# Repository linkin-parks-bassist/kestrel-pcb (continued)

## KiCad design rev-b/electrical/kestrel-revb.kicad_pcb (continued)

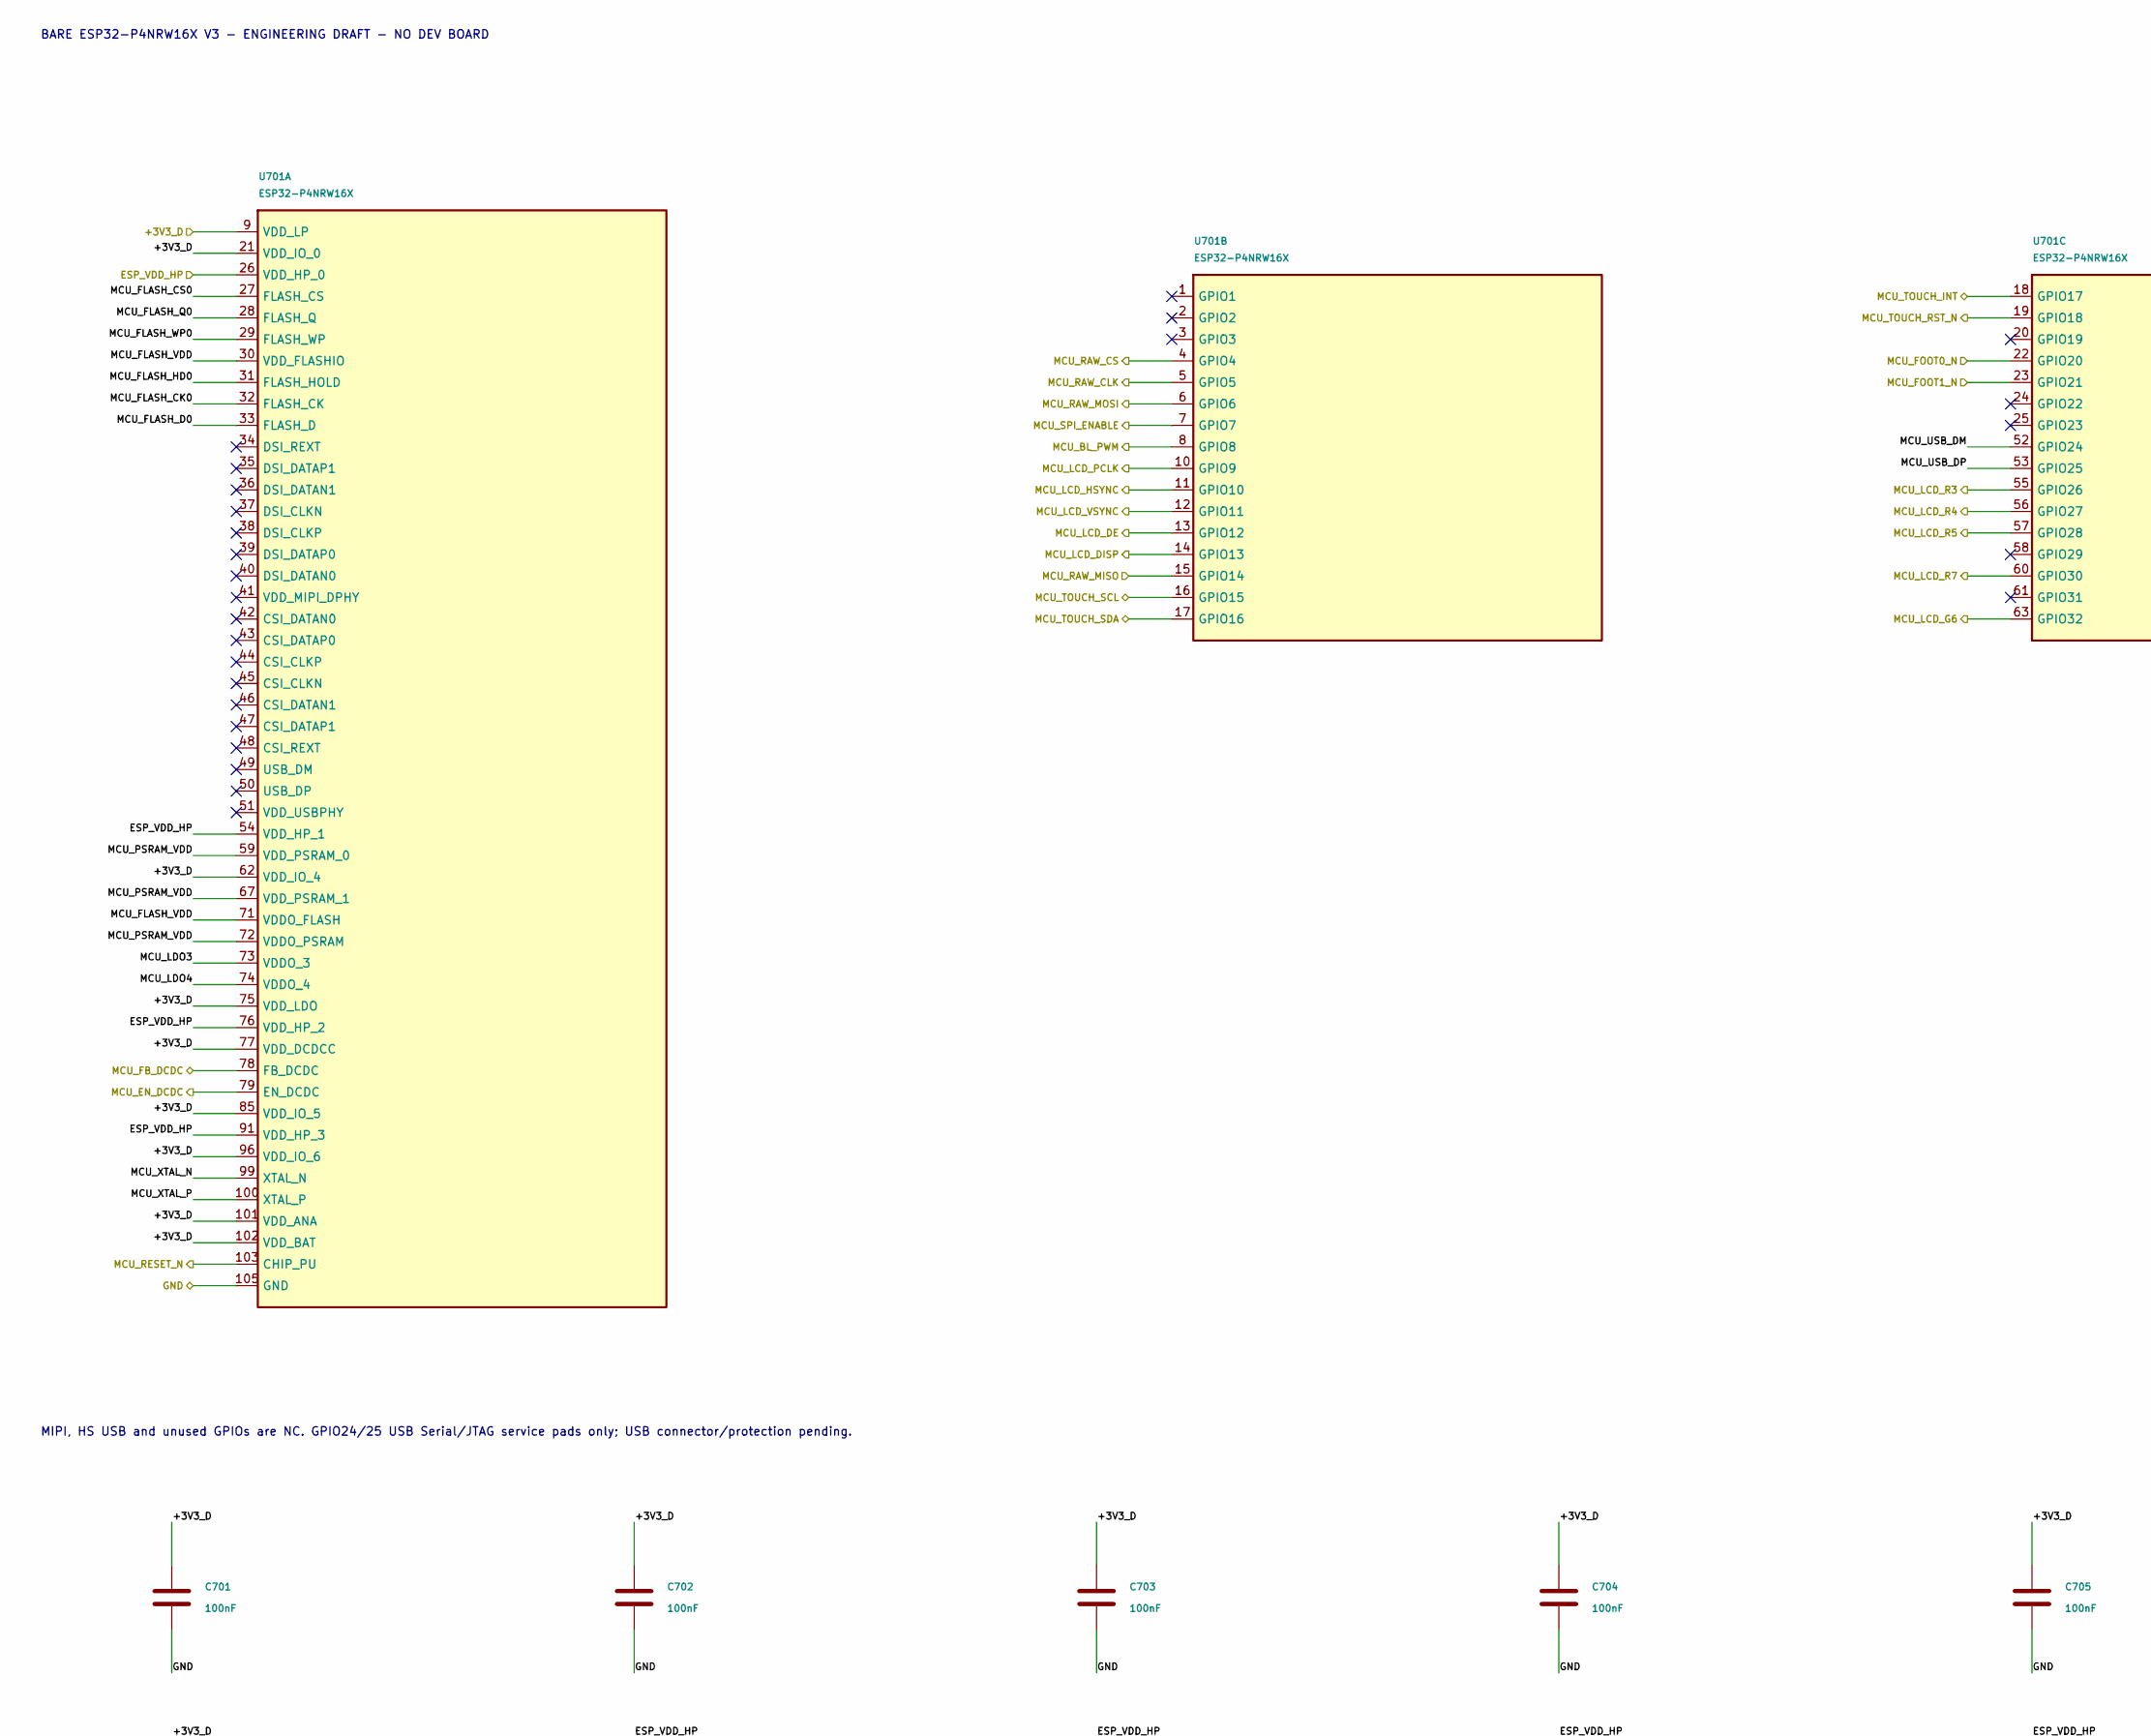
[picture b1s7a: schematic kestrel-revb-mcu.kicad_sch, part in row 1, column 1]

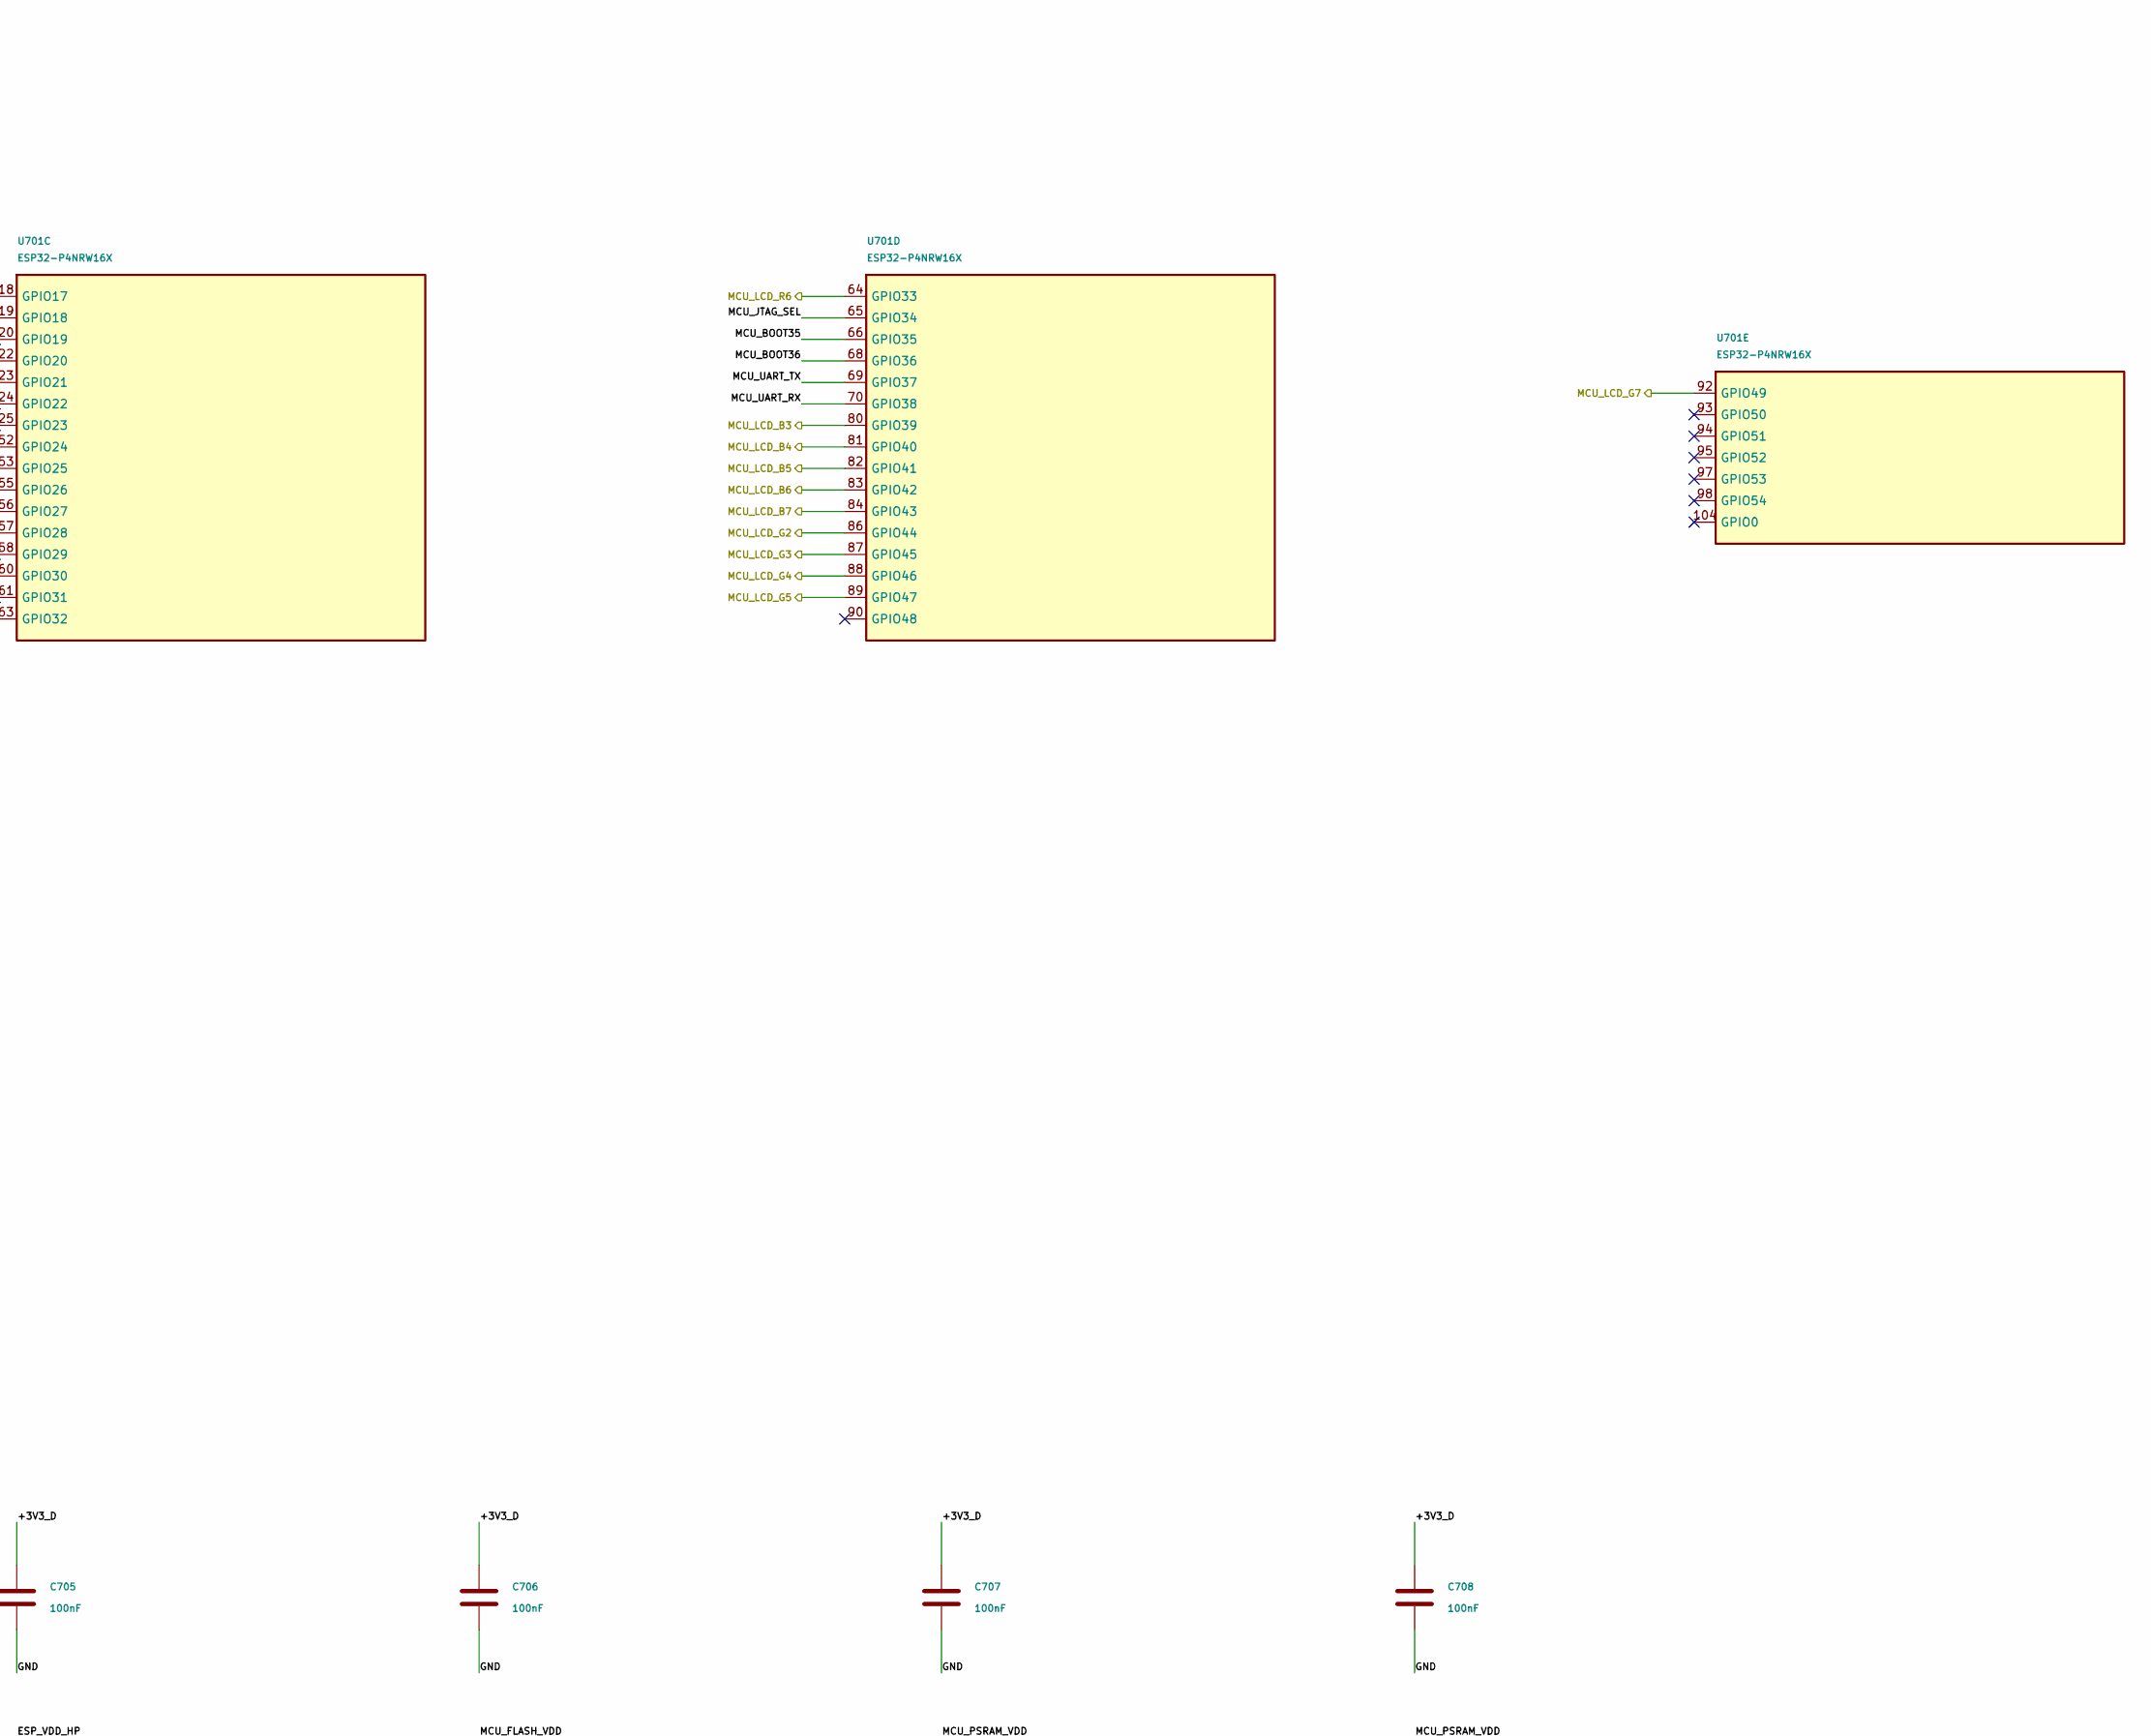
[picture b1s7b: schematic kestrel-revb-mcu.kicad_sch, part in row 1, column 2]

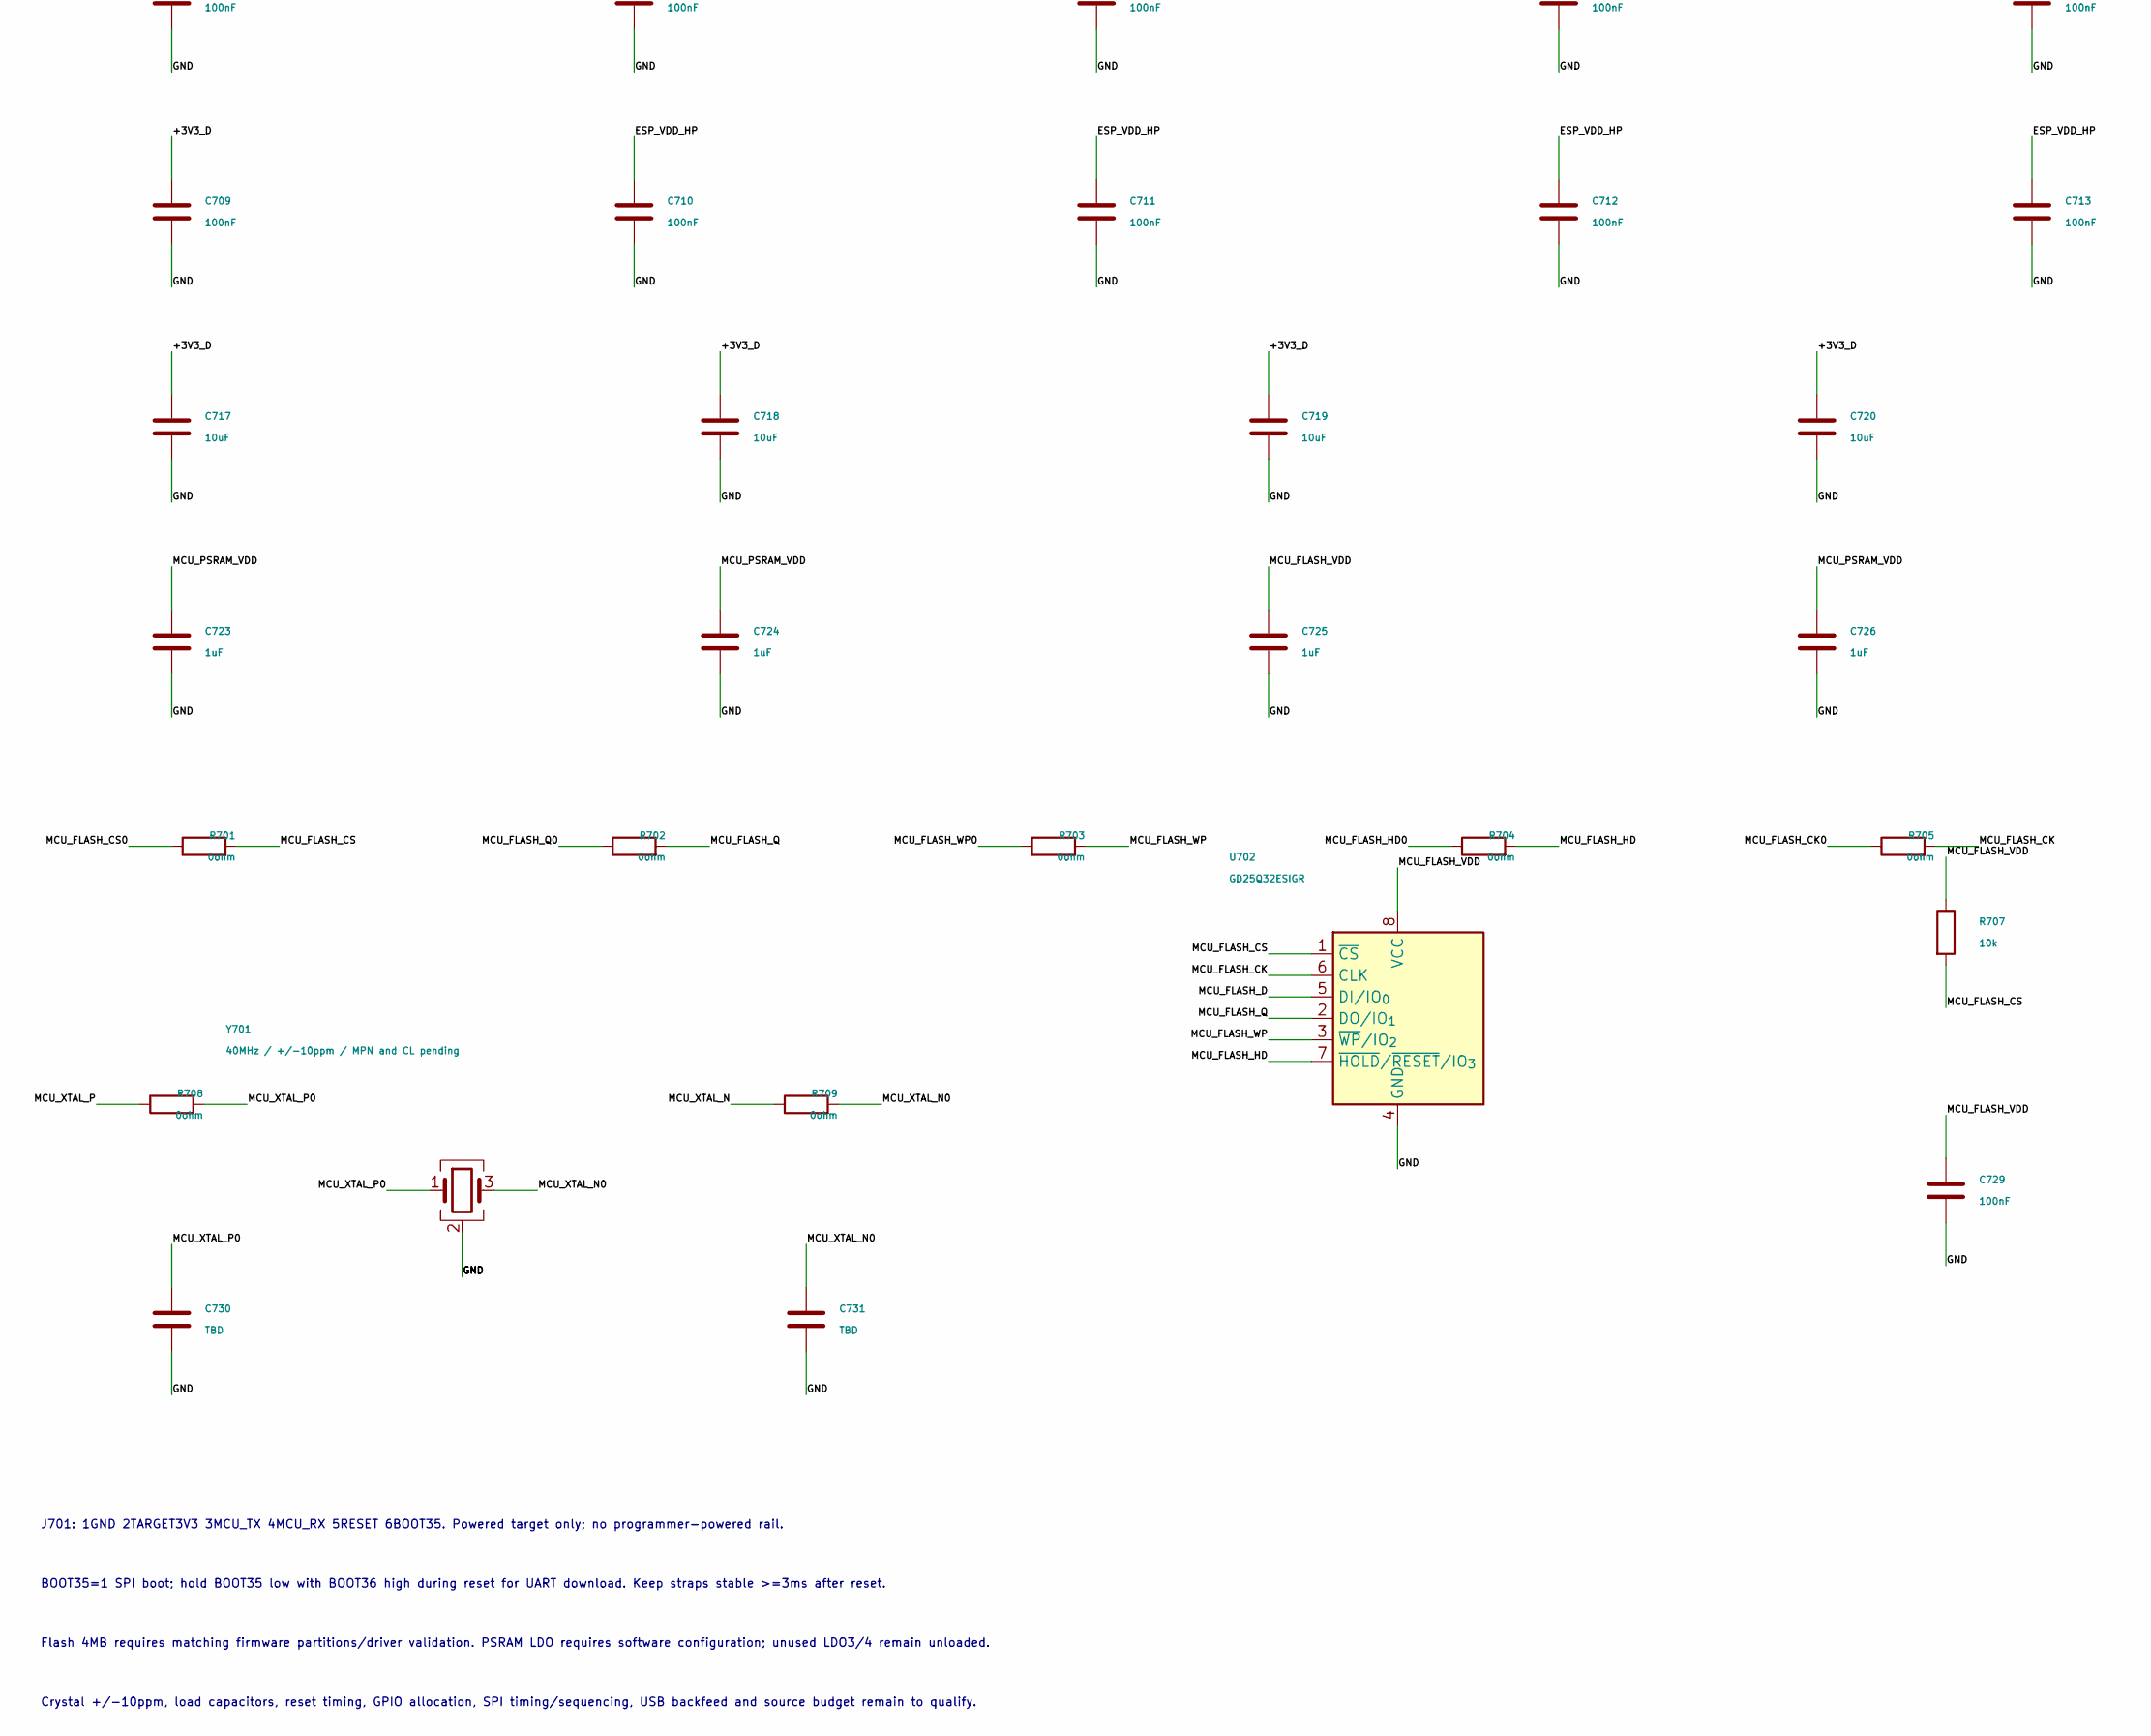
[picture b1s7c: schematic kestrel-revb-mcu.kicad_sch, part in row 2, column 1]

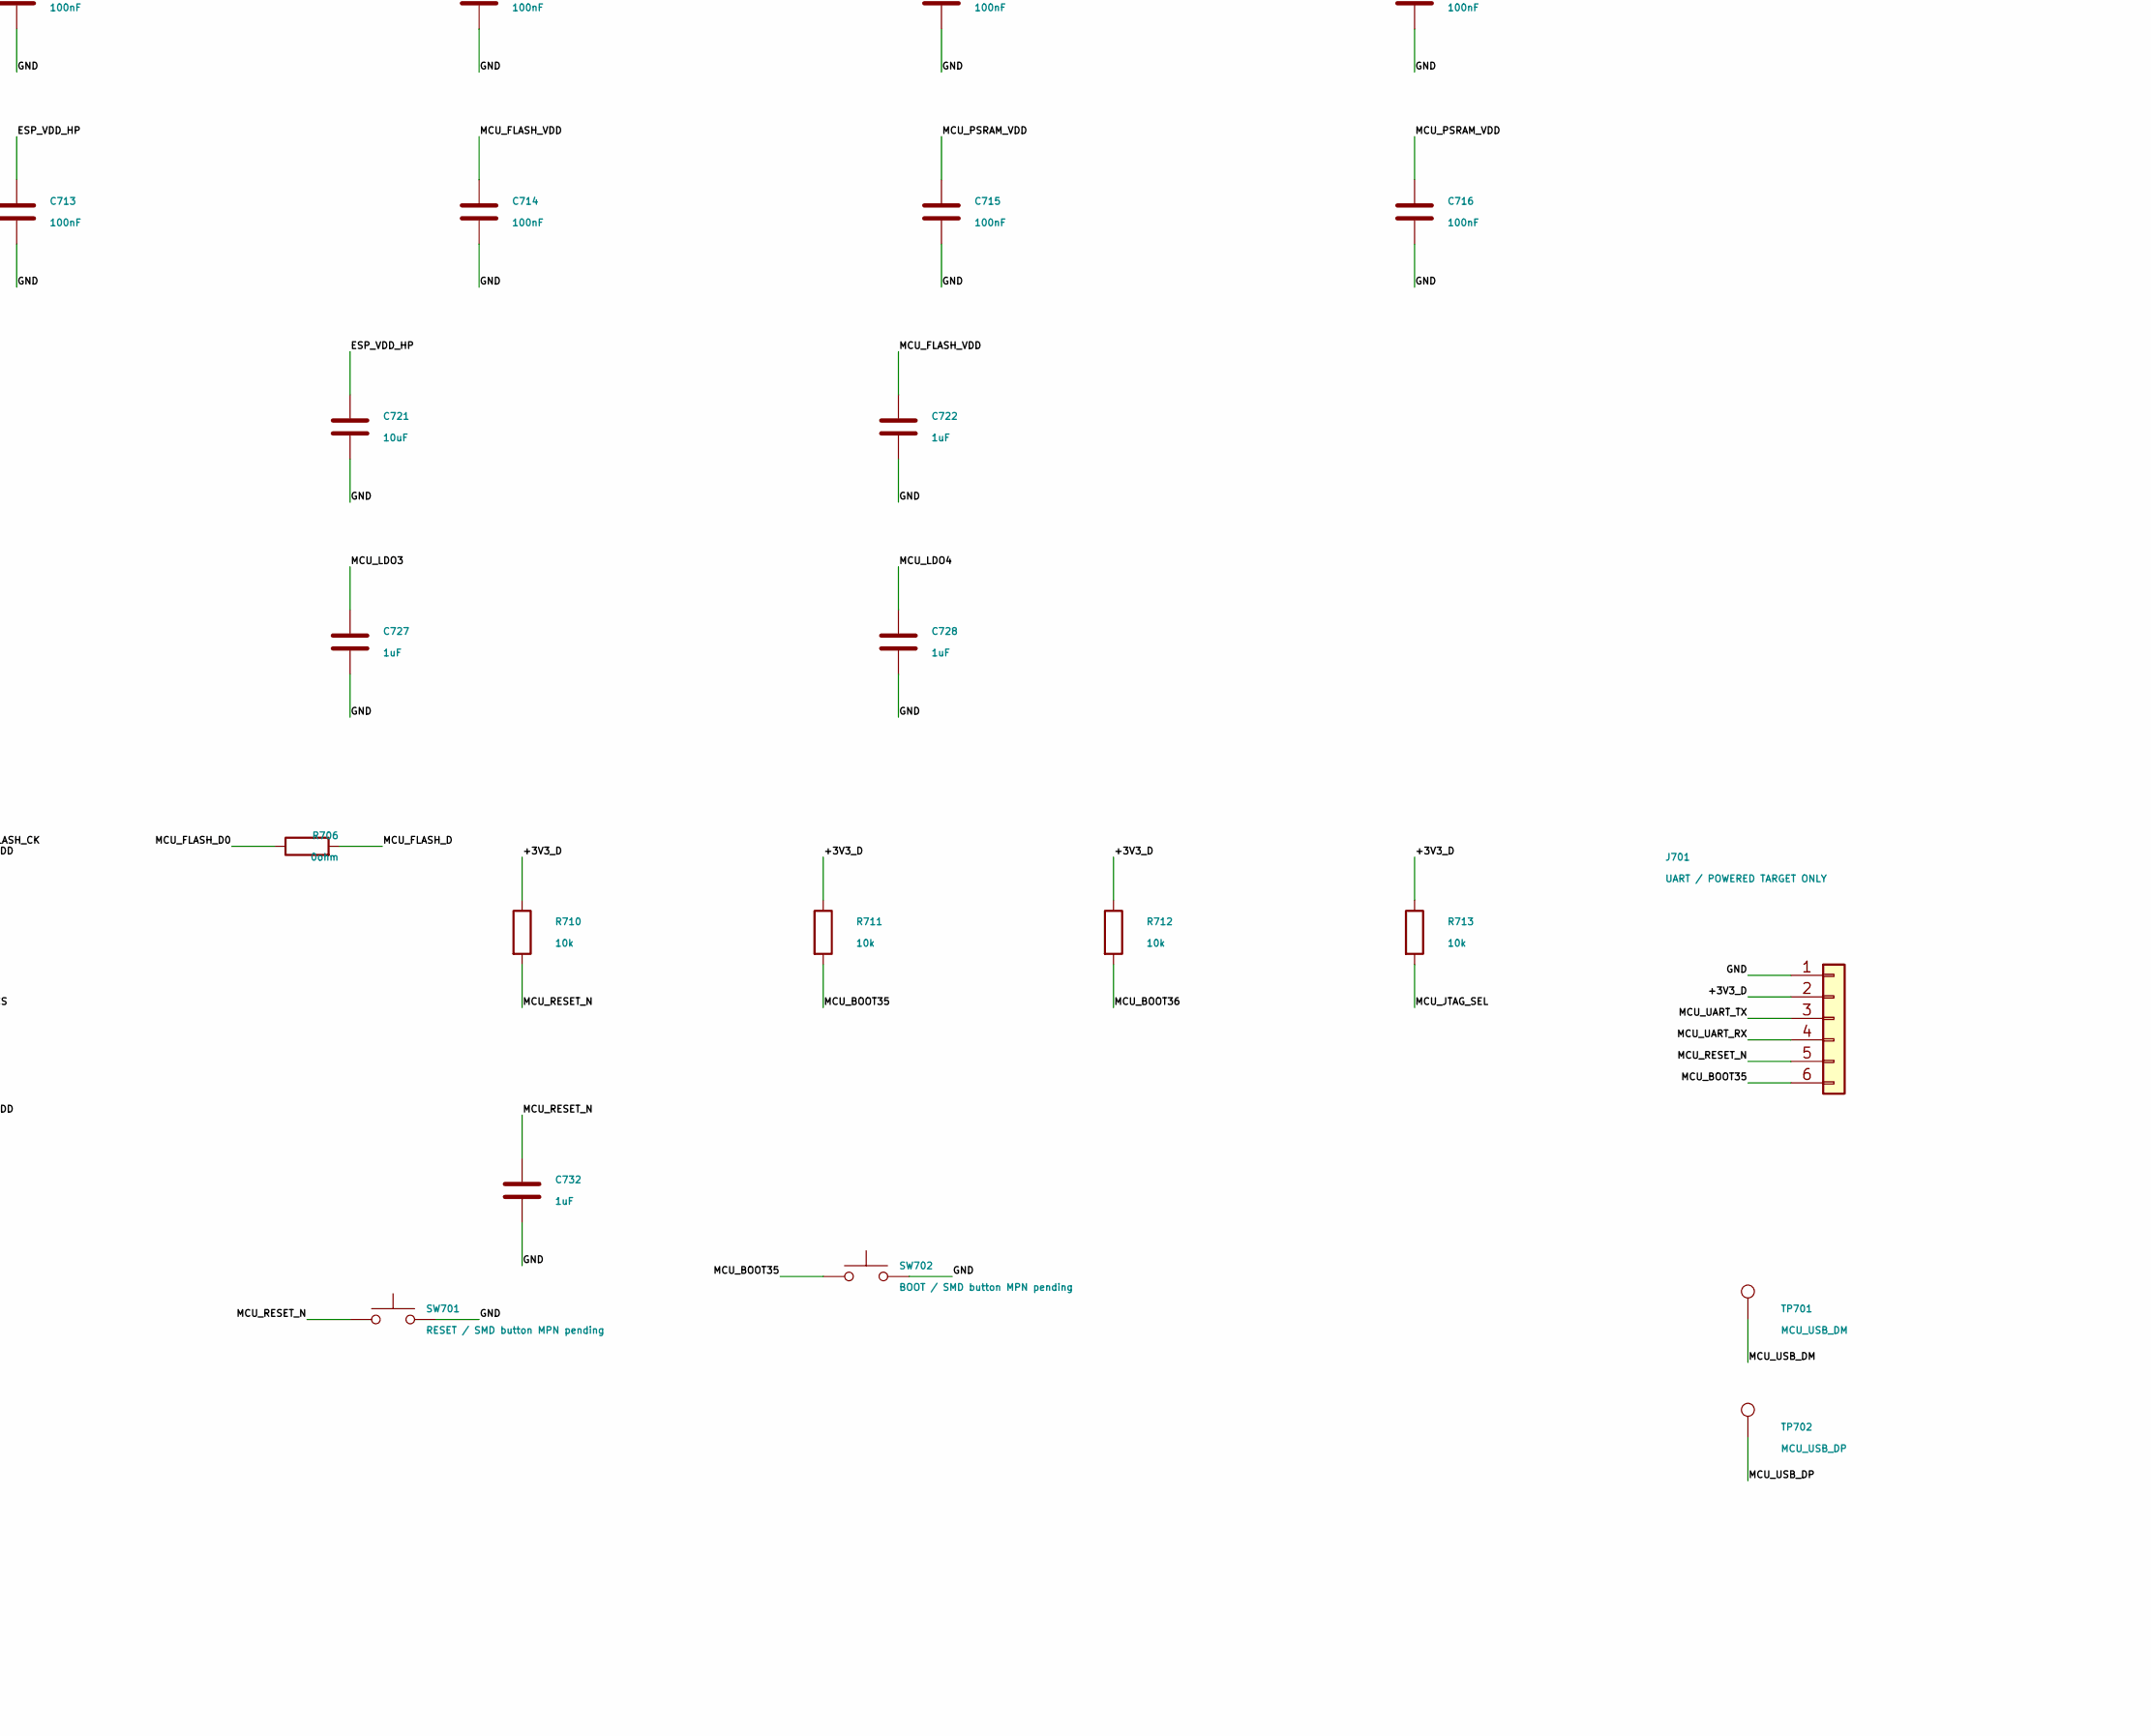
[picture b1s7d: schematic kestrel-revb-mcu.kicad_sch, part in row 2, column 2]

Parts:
C701: 100nF; C_0402_1005Metric; Rating 100nF / 16V X7R +/-10% / at U701 pin 9; MPN CL05B104KO5NNNC; LCSC C1525
C702: 100nF; C_0402_1005Metric; Rating 100nF / 16V X7R +/-10% / at U701 pin 21; MPN CL05B104KO5NNNC; LCSC C1525
C703: 100nF; C_0402_1005Metric; Rating 100nF / 16V X7R +/-10% / at U701 pin 62; MPN CL05B104KO5NNNC; LCSC C1525
C704: 100nF; C_0402_1005Metric; Rating 100nF / 16V X7R +/-10% / at U701 pin 85; MPN CL05B104KO5NNNC; LCSC C1525
C705: 100nF; C_0402_1005Metric; Rating 100nF / 16V X7R +/-10% / at U701 pin 96; MPN CL05B104KO5NNNC; LCSC C1525
C706: 100nF; C_0402_1005Metric; Rating 100nF / 16V X7R +/-10% / at U701 pin 101; MPN CL05B104KO5NNNC; LCSC C1525
C707: 100nF; C_0402_1005Metric; Rating 100nF / 16V X7R +/-10% / at U701 pin 102; MPN CL05B104KO5NNNC; LCSC C1525
C708: 100nF; C_0402_1005Metric; Rating 100nF / 16V X7R +/-10% / at U701 pin 75; MPN CL05B104KO5NNNC; LCSC C1525
C709: 100nF; C_0402_1005Metric; Rating 100nF / 16V X7R +/-10% / at U701 pin 77; MPN CL05B104KO5NNNC; LCSC C1525
C710: 100nF; C_0402_1005Metric; Rating 100nF / 16V X7R +/-10% / at U701 pin 26; MPN CL05B104KO5NNNC; LCSC C1525
C711: 100nF; C_0402_1005Metric; Rating 100nF / 16V X7R +/-10% / at U701 pin 54; MPN CL05B104KO5NNNC; LCSC C1525
C712: 100nF; C_0402_1005Metric; Rating 100nF / 16V X7R +/-10% / at U701 pin 76; MPN CL05B104KO5NNNC; LCSC C1525
C713: 100nF; C_0402_1005Metric; Rating 100nF / 16V X7R +/-10% / at U701 pin 91; MPN CL05B104KO5NNNC; LCSC C1525
C714: 100nF; C_0402_1005Metric; Rating 100nF / 16V X7R +/-10% / at U701 pin 30; MPN CL05B104KO5NNNC; LCSC C1525
C715: 100nF; C_0402_1005Metric; Rating 100nF / 16V X7R +/-10% / at U701 pin 59; MPN CL05B104KO5NNNC; LCSC C1525
C716: 100nF; C_0402_1005Metric; Rating 100nF / 16V X7R +/-10% / at U701 pin 67; MPN CL05B104KO5NNNC; LCSC C1525
C717: 10uF; C_0805_2012Metric; Rating 10uF / 16V X7R
C718: 10uF; C_0805_2012Metric; Rating 10uF / 16V X7R / near VDD_BAT102
C719: 10uF; C_0805_2012Metric; Rating 10uF / 16V X7R / near VDD_LDO75
C720: 10uF; C_0805_2012Metric; Rating 10uF / 16V X7R / near VDD_DCDCC77
C721: 10uF; C_0805_2012Metric; Rating 10uF / 16V X7R / local HP bulk
C722: 1uF; C_0805_2012Metric; Rating 1uF / 16V X7R / at FLASHIO30
C723: 1uF; C_0805_2012Metric; Rating 1uF / 16V X7R / at PSRAM59
C724: 1uF; C_0805_2012Metric; Rating 1uF / 16V X7R / at PSRAM67
C725: 1uF; C_0805_2012Metric; Rating 1uF / 16V X7R / at VDDO_FLASH71
C726: 1uF; C_0805_2012Metric; Rating 1uF / 16V X7R / at VDDO_PSRAM72
C727: 1uF; C_0805_2012Metric; Rating 1uF / 16V X7R / at VDDO3_73
C728: 1uF; C_0805_2012Metric; Rating 1uF / 16V X7R / at VDDO4_74
C729: 100nF; C_0603_1608Metric; Rating 100nF / 16V X7R / at flash VCC
C730, C731: TBD; C_0603_1608Metric; Rating TBD / crystal CL and stray / C0G
C732: 1uF; C_0603_1608Metric; Rating 1uF / 16V X7R / reset RC starting point
J701: UART / POWERED TARGET ONLY; PinHeader_1x06_P2.54mm_Vertical
R701, R702, R703, R704, R705, R706: 0ohm; R_0603_1608Metric; Rating 0ohm / flash tuning footprint
R707: 10k; R_0603_1608Metric; Rating 10k / 1% / flash CS pullup
R708, R709: 0ohm; R_0402_1005Metric; Rating 0ohm / crystal tuning
R710, R711, R712, R713: 10k; R_0603_1608Metric; Rating 10k / 1%
SW701: RESET / SMD button MPN pending; SW_SPST_TL3342
SW702: BOOT / SMD button MPN pending; SW_SPST_TL3342
TP701: MCU_USB_DM; TestPoint_Pad_D1.0mm
TP702: MCU_USB_DP; TestPoint_Pad_D1.0mm
U701: ESP32-P4NRW16X; ESP32_P4_QFN104_10x10_P0.35_EP7.5
U702: GD25Q32ESIGR; SOIC-8_5.3x5.3mm_P1.27mm
Y701: 40MHz / +/-10ppm / MPN and CL pending; Crystal_SMD_3225-4Pin_3.2x2.5mm

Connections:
/+3V3_D: C701.1, C702.1, C703.1, C704.1, C705.1, C706.1, C707.1, C708.1, C709.1, C717.1, C718.1, C719.1, C720.1, J701.2, R710.1, R711.1, R712.1, R713.1, U701.9 (VDD_LP), U701.21 (VDD_IO_0), U701.62 (VDD_IO_4), U701.75 (VDD_LDO), U701.77 (VDD_DCDCC), U701.85 (VDD_IO_5), U701.96 (VDD_IO_6), U701.101 (VDD_ANA), U701.102 (VDD_BAT); also elsewhere on the board
/Bare ESP32-P4 support/MCU_BOOT35: J701.6, R711.2, SW702.1, U701.66 (GPIO35)
/Bare ESP32-P4 support/MCU_BOOT36: R712.2, U701.68 (GPIO36)
/Bare ESP32-P4 support/MCU_FLASH_CK: R705.2, U702.6 (CLK)
/Bare ESP32-P4 support/MCU_FLASH_CK0: R705.1, U701.32 (FLASH_CK)
/Bare ESP32-P4 support/MCU_FLASH_CS: R701.2, R707.2, U702.1 (~CS)
/Bare ESP32-P4 support/MCU_FLASH_CS0: R701.1, U701.27 (FLASH_CS)
/Bare ESP32-P4 support/MCU_FLASH_D: R706.2, U702.5 (DI/IO_{0})
/Bare ESP32-P4 support/MCU_FLASH_D0: R706.1, U701.33 (FLASH_D)
/Bare ESP32-P4 support/MCU_FLASH_HD: R704.2, U702.7 (~HOLD/~RESET/IO_{3})
/Bare ESP32-P4 support/MCU_FLASH_HD0: R704.1, U701.31 (FLASH_HOLD)
/Bare ESP32-P4 support/MCU_FLASH_Q: R702.2, U702.2 (DO/IO_{1})
/Bare ESP32-P4 support/MCU_FLASH_Q0: R702.1, U701.28 (FLASH_Q)
/Bare ESP32-P4 support/MCU_FLASH_VDD: C714.1, C722.1, C725.1, C729.1, R707.1, U701.30 (VDD_FLASHIO), U701.71 (VDDO_FLASH), U702.8 (VCC)
/Bare ESP32-P4 support/MCU_FLASH_WP: R703.2, U702.3 (~WP/IO_{2})
/Bare ESP32-P4 support/MCU_FLASH_WP0: R703.1, U701.29 (FLASH_WP)
/Bare ESP32-P4 support/MCU_JTAG_SEL: R713.2, U701.65 (GPIO34)
/Bare ESP32-P4 support/MCU_LDO3: C727.1, U701.73 (VDDO_3)
/Bare ESP32-P4 support/MCU_LDO4: C728.1, U701.74 (VDDO_4)
/Bare ESP32-P4 support/MCU_PSRAM_VDD: C715.1, C716.1, C723.1, C724.1, C726.1, U701.59 (VDD_PSRAM_0), U701.67 (VDD_PSRAM_1), U701.72 (VDDO_PSRAM)
/Bare ESP32-P4 support/MCU_UART_RX: J701.4, U701.70 (GPIO38)
/Bare ESP32-P4 support/MCU_UART_TX: J701.3, U701.69 (GPIO37)
/Bare ESP32-P4 support/MCU_USB_DM: TP701.1, U701.52 (GPIO24)
/Bare ESP32-P4 support/MCU_USB_DP: TP702.1, U701.53 (GPIO25)
/Bare ESP32-P4 support/MCU_XTAL_N: R709.1, U701.99 (XTAL_N)
/Bare ESP32-P4 support/MCU_XTAL_N0: C731.1, R709.2, Y701.3
/Bare ESP32-P4 support/MCU_XTAL_P: R708.1, U701.100 (XTAL_P)
/Bare ESP32-P4 support/MCU_XTAL_P0: C730.1, R708.2, Y701.1
/ESP_VDD_HP: C710.1, C711.1, C712.1, C713.1, C721.1, U701.26 (VDD_HP_0), U701.54 (VDD_HP_1), U701.76 (VDD_HP_2), U701.91 (VDD_HP_3); also elsewhere on the board
/GND: C701.2, C702.2, C703.2, C704.2, C705.2, C706.2, C707.2, C708.2, C709.2, C710.2, C711.2, C712.2, C713.2, C714.2, C715.2, C716.2, C717.2, C718.2, C719.2, C720.2, C721.2, C722.2, C723.2, C724.2, C725.2, C726.2, C727.2, C728.2, C729.2, C730.2, C731.2, C732.2, J701.1, SW701.2, SW702.2, U701.105 (GND), U702.4 (GND), Y701.2 (G), Y701.4 (G); also elsewhere on the board
/MCU_BL_PWM: U701.8 (GPIO8); also elsewhere on the board
/MCU_EN_DCDC: U701.79 (EN_DCDC); also elsewhere on the board
/MCU_FB_DCDC: U701.78 (FB_DCDC); also elsewhere on the board
/MCU_FOOT0_N: U701.22 (GPIO20); also elsewhere on the board
/MCU_FOOT1_N: U701.23 (GPIO21); also elsewhere on the board
/MCU_LCD_B3: U701.80 (GPIO39); also elsewhere on the board
/MCU_LCD_B4: U701.81 (GPIO40); also elsewhere on the board
/MCU_LCD_B5: U701.82 (GPIO41); also elsewhere on the board
/MCU_LCD_B6: U701.83 (GPIO42); also elsewhere on the board
/MCU_LCD_B7: U701.84 (GPIO43); also elsewhere on the board
/MCU_LCD_DE: U701.13 (GPIO12); also elsewhere on the board
/MCU_LCD_DISP: U701.14 (GPIO13); also elsewhere on the board
/MCU_LCD_G2: U701.86 (GPIO44); also elsewhere on the board
/MCU_LCD_G3: U701.87 (GPIO45); also elsewhere on the board
/MCU_LCD_G4: U701.88 (GPIO46); also elsewhere on the board
/MCU_LCD_G5: U701.89 (GPIO47); also elsewhere on the board
/MCU_LCD_G6: U701.63 (GPIO32); also elsewhere on the board
/MCU_LCD_G7: U701.92 (GPIO49); also elsewhere on the board
/MCU_LCD_HSYNC: U701.11 (GPIO10); also elsewhere on the board
/MCU_LCD_PCLK: U701.10 (GPIO9); also elsewhere on the board
/MCU_LCD_R3: U701.55 (GPIO26); also elsewhere on the board
/MCU_LCD_R4: U701.56 (GPIO27); also elsewhere on the board
/MCU_LCD_R5: U701.57 (GPIO28); also elsewhere on the board
/MCU_LCD_R6: U701.64 (GPIO33); also elsewhere on the board
/MCU_LCD_R7: U701.60 (GPIO30); also elsewhere on the board
/MCU_LCD_VSYNC: U701.12 (GPIO11); also elsewhere on the board
/MCU_RAW_CLK: U701.5 (GPIO5); also elsewhere on the board
/MCU_RAW_CS: U701.4 (GPIO4); also elsewhere on the board
/MCU_RAW_MISO: U701.15 (GPIO14); also elsewhere on the board
/MCU_RAW_MOSI: U701.6 (GPIO6); also elsewhere on the board
/MCU_RESET_N: C732.1, J701.5, R710.2, SW701.1, U701.103 (CHIP_PU); also elsewhere on the board
/MCU_SPI_ENABLE: U701.7 (GPIO7); also elsewhere on the board
/MCU_TOUCH_INT: U701.18 (GPIO17); also elsewhere on the board
/MCU_TOUCH_RST_N: U701.19 (GPIO18); also elsewhere on the board
/MCU_TOUCH_SCL: U701.16 (GPIO15); also elsewhere on the board
/MCU_TOUCH_SDA: U701.17 (GPIO16); also elsewhere on the board

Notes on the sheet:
BARE ESP32-P4NRW16X V3 - ENGINEERING DRAFT - NO DEV BOARD
MIPI, HS USB and unused GPIOs are NC. GPIO24/25 USB Serial/JTAG service pads only; USB connector/protection pending.
J701: 1GND 2TARGET3V3 3MCU_TX 4MCU_RX 5RESET 6BOOT35. Powered target only; no programmer-powered rail.
BOOT35=1 SPI boot; hold BOOT35 low with BOOT36 high during reset for UART download. Keep straps stable >=3ms after reset.
Flash 4MB requires matching firmware partitions/driver validation. PSRAM LDO requires software configuration; unused LDO3/4 remain unloaded.
Crystal +/-10ppm, load capacitors, reset timing, GPIO allocation, SPI timing/sequencing, USB backfeed and source budget remain to qualify.
